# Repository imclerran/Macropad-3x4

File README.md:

# Design for a 3x4 Macropad with 2 rotary encoders

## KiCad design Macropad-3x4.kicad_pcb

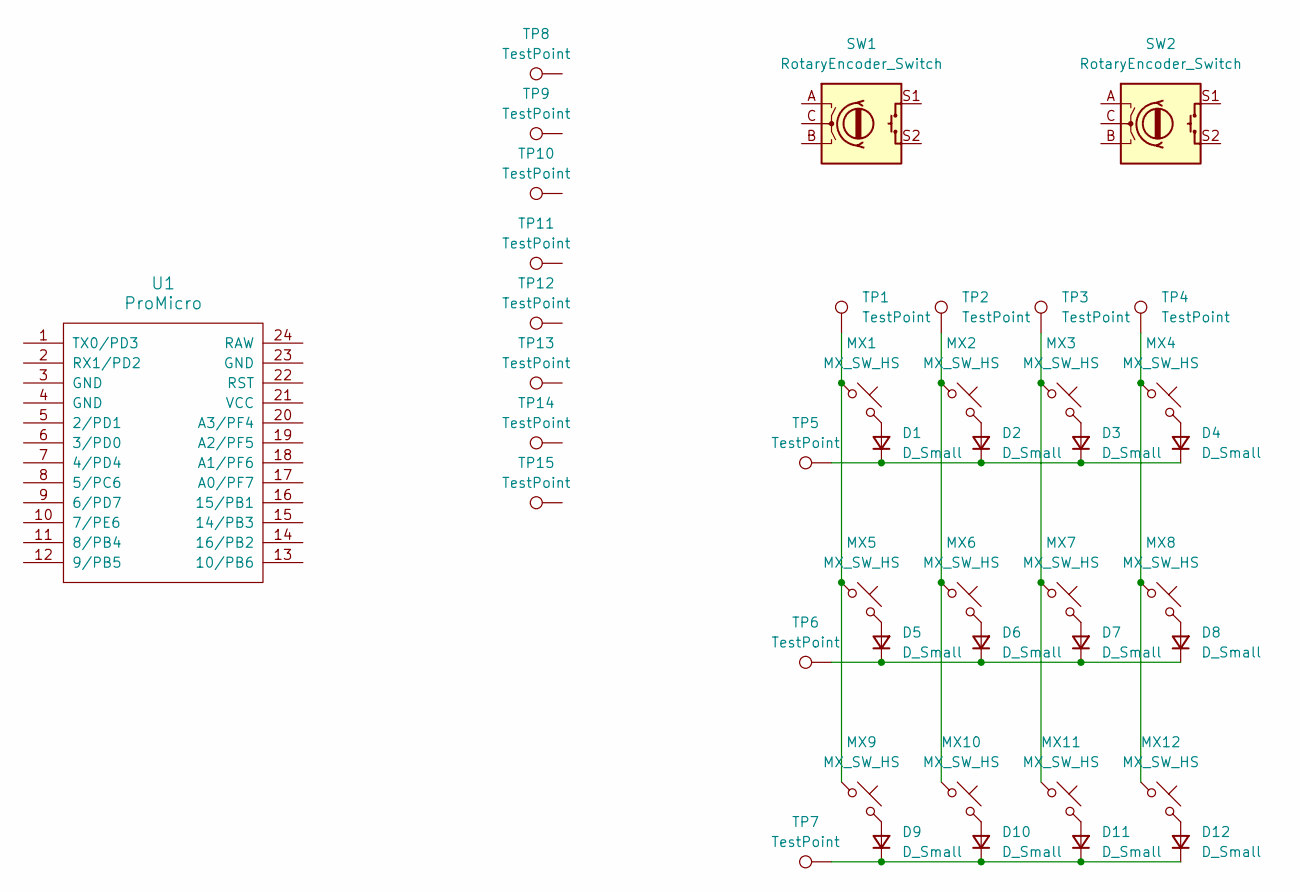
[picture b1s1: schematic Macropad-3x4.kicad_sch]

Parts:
D1, D2, D3, D4, D5, D6, D7, D8, D9, D10, D11, D12: D_Small; D_SOD-123
MX1, MX2, MX3, MX4, MX5, MX6, MX7, MX8, MX9, MX10, MX11, MX12: MX_SW_HS; SW_MX_HS_1u
SW1, SW2: RotaryEncoder_Switch; RotaryEncoder_EC11
TP1, TP2, TP3, TP4, TP5, TP6, TP7, TP8, TP9, TP10, TP11, TP12, TP13, TP14, TP15: TestPoint; TestPoint_Pad_3.0x3.0mm
U1: ProMicro; ArduinoProMicro

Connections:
unnamed: D1.2 (A), MX1.2
unnamed: D1.1 (K), D2.1 (K), D3.1 (K), D4.1 (K), TP5.1
unnamed: D2.2 (A), MX2.2
unnamed: D3.2 (A), MX3.2
unnamed: D4.2 (A), MX4.2
unnamed: D5.2 (A), MX5.2
unnamed: D5.1 (K), D6.1 (K), D7.1 (K), D8.1 (K), TP6.1
unnamed: D6.2 (A), MX6.2
unnamed: D7.2 (A), MX7.2
unnamed: D8.2 (A), MX8.2
unnamed: D9.2 (A), MX9.2
unnamed: D10.2 (A), MX10.2
unnamed: D9.1 (K), D10.1 (K), D11.1 (K), D12.1 (K), TP7.1
unnamed: D11.2 (A), MX11.2
unnamed: D12.2 (A), MX12.2
unnamed: MX1.1, MX5.1, MX9.1, TP1.1
unnamed: MX2.1, MX6.1, MX10.1, TP2.1
unnamed: MX3.1, MX7.1, MX11.1, TP3.1
unnamed: MX4.1, MX8.1, MX12.1, TP4.1

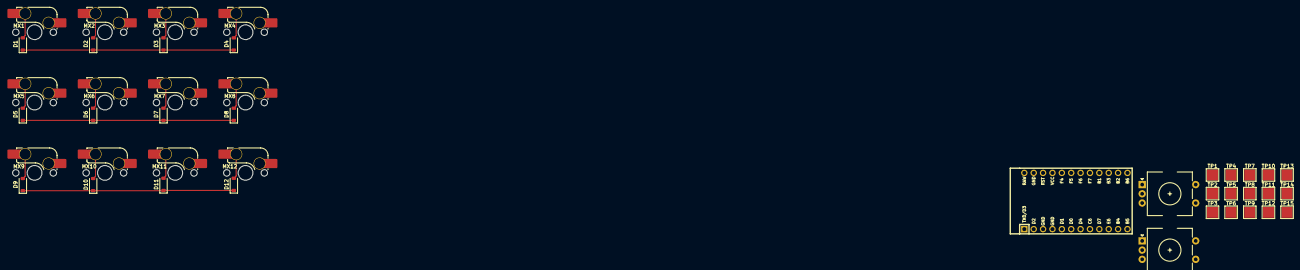
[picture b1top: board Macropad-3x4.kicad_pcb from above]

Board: 2 copper layers, 42 parts (0 on the bottom side), 19 nets.

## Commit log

2023-10-27 initialized KiCad project and switch libraries
2023-10-31 basic circuit schematic
2023-10-31 begin placing components on pcb
